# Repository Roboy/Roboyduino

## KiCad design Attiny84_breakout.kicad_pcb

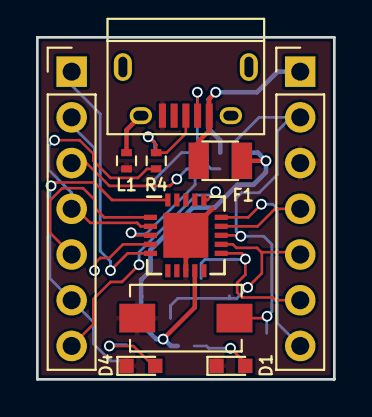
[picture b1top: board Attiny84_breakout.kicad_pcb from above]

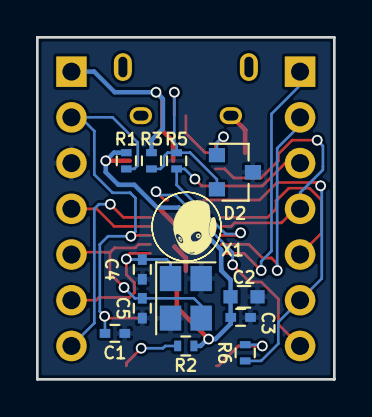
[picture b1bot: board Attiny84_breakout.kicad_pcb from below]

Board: 2 copper layers, 16.5 x 19.0 mm, 23 parts (13 on the bottom side), 20 nets.

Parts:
C1, C3: 100n; C_0402
C2: 10u; C_0603
C4, C5: 22p; C_0402
D1, D4: LED; LED_0603
D2: D_3V6; D_SOT-23_NKA
F1: Polyfuse_Small; Fuse_SMD1206_Reflow
IC1: ATTINY84A-M; QFN-20-1EP_4x4mm_Pitch0.5mm
J1: USB_OTG; USB_Micro-B
L1: Ferrite_Bead_Small; L_0402
P2, P3: CONN_01X07; Pin_Header_Straight_1x07_Pitch2.54mm
R1: 10k; R_0402
R2, R6: 1k; R_0402
R3: 1.5K; R_0402
R4, R5: 68; R_0402
SW1: SW_PUSH; SW_SPST_EVQPE1
X1: CRYSTAL_SMD; Crystal_SMD_3225-4pin_3.2x2.5mm
svg2mod: G***; Roboy_Logo_F.SilkS

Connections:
+5V: F1.1, J1.1, P3.1, R3.2
GND: C1.2, C2.2, C3.2, C4.2, C5.2, D1.1, D2.2, D4.1, IC1.8, IC1.21, J1.5, L1.1, P3.3, SW1.1, X1.2, X1.4
unnamed: C1.1, IC1.13, P3.2, R1.2, SW1.2
unnamed: C2.1, C3.1, F1.2, IC1.9, R1.1, R2.1
unnamed: C4.1, IC1.11, P3.6, X1.1
unnamed: C5.1, IC1.12, P3.5, X1.3
unnamed: D1.2, R2.2
unnamed: D2.1, J1.2, R3.1, R5.2
unnamed: D2.3, J1.3, R4.2
unnamed: D4.2, R6.2
unnamed: IC1.1, P2.5
unnamed: IC1.2, P2.4, R4.1
unnamed: IC1.3, P2.3, R5.1
unnamed: IC1.4, P2.2
unnamed: IC1.5, P2.1
unnamed: IC1.14, P3.4
unnamed: IC1.15, P3.7
unnamed: IC1.16, P2.7
unnamed: IC1.20, P2.6, R6.1
unnamed: J1.6, L1.2

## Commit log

2017-07-29 Initial commit with half finished board without routing
2017-08-03 Added usb port, and some other functions and circuit protection
2017-08-07 Corrected grid and dimensions to fit in a standard breadboard
2017-08-10 Partial routing completed
2017-08-13 Finished routing
2017-08-14 Fixed some dimension problems for fabrication, final touches: silkscreen, cool logo ...
2018-01-18 Minor changes. Updated BOM
2019-01-22 Added BOM and some pictures.
